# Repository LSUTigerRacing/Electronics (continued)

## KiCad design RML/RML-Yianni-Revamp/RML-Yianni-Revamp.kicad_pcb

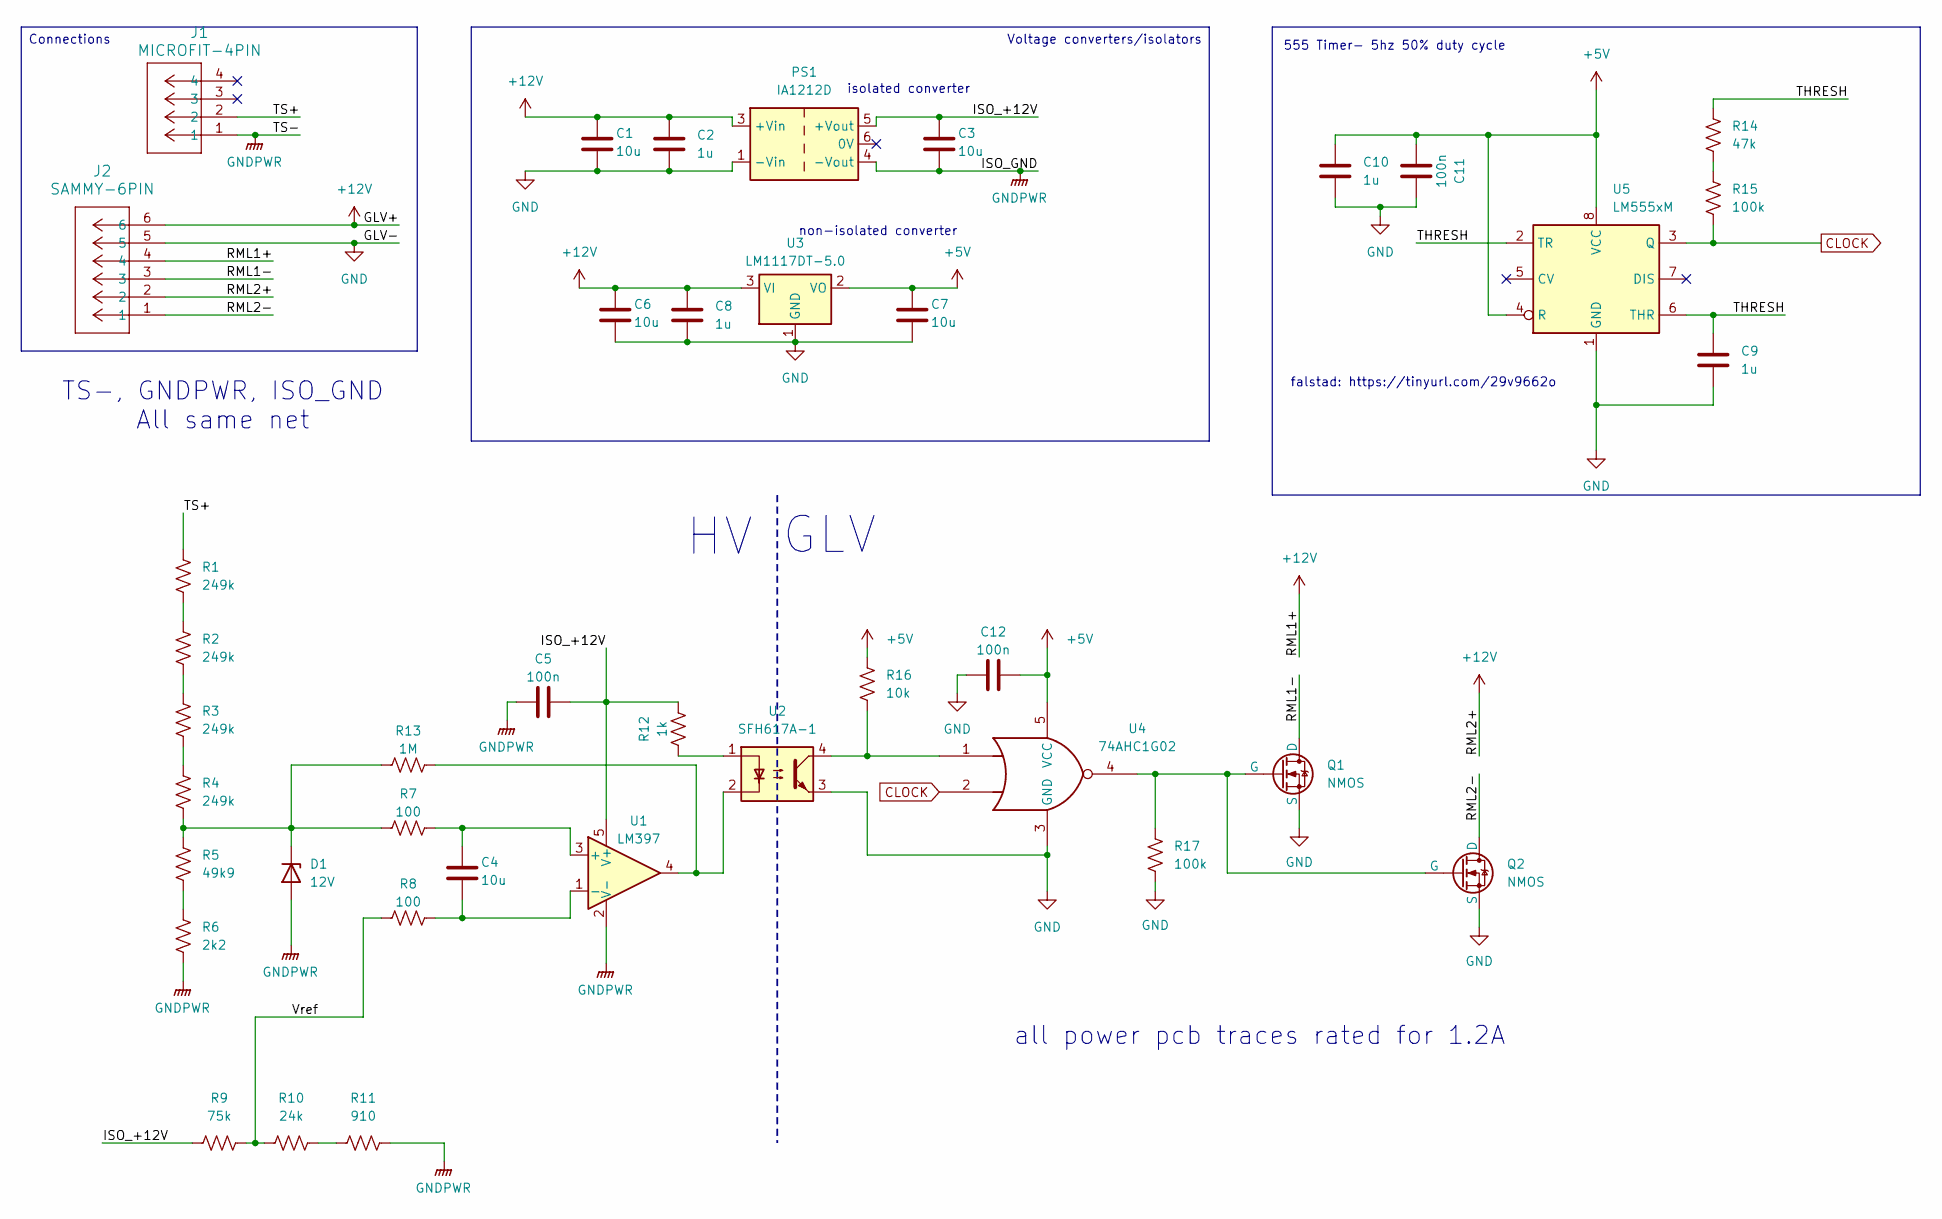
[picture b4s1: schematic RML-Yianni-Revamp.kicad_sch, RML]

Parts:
C1, C3, C4, C6, C7: 10u; C_0603_1608Metric; JLC# C70225
C2, C8, C9, C10: 1u; C_0603_1608Metric; JLC# C1592
C5, C11, C12: 100n; C_0603_1608Metric; JLC# C1590
D1: 12V; D_SOD-123; JLC# C43491
J1: MICROFIT-4PIN
J2: SAMMY-6PIN
PS1: IA1212D; Converter_DCDC_XP_POWER-IAxxxxD_THT
Q1, Q2: NMOS; SOT-23; JLC# C2590
R1, R2, R3, R4: 249k; R_1206_3216Metric; JLC C34578
R5: 49k9; R_1206_3216Metric; JLC# C18017
R6: 2k2; R_1206_3216Metric; JLC# C17948
R7, R8: 100; R_1206_3216Metric; JLC# C17901
R9: 75k; R_1206_3216Metric; JLC# C17986
R10: 24k; R_1206_3216Metric; JLC# C17960
R11: 910; R_1206_3216Metric; JLC# C137224
R12: 1k; R_1206_3216Metric; JLC# C1469
R13: 1M; R_1206_3216Metric; JLC# C17927
R14: 47k; R_1206_3216Metric; JLC# C25664
R15, R17: 100k; R_1206_3216Metric; JLC# C17900
R16: 10k; R_1206_3216Metric; JLC# C1489
U1: LM397; SOT-23-5; JLC# C132076
U2: SFH617A-1; DIP-4_W7.62mm; MOUSER SFH617A-1
U3: LM1117DT-5.0; TO-252-3_TabPin2; JLC# C354068
U4: 74AHC1G02; SOT-23-5; JLC# C7463
U5: LM555xM; SOIC-8_3.9x4.9mm_P1.27mm; JLC# C90760

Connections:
+5V: C7.1, C10.1, C11.1, C12.2, R16.1, U3.2 (VO), U4.5 (VCC), U5.4 (R), U5.8 (VCC)
+12V: C1.1, C2.1, C6.1, C8.1, J2.2, J2.4, J2.6, PS1.3 (+Vin), U3.3 (VI)
/ISO_+12V: C3.1, C5.2, PS1.5 (+Vout), R9.1, R12.2, U1.5 (V+)
/RML1-: J2.3, Q1.1 (D)
/RML2-: J2.1, Q2.1 (D)
/THRESH: C9.1, R14.1, U5.2 (TR), U5.6 (THR)
/TS+: J1.2, R1.1
/Vref: R8.1, R9.2, R10.1
CLOCK: R15.2, U4.2, U5.3 (Q)
GND: C1.2, C2.2, C6.2, C7.2, C8.2, C9.2, C10.2, C11.2, C12.1, J2.5, PS1.1 (-Vin), Q1.3 (S), Q2.3 (S), R17.1, U2.3, U3.1 (GND), U4.3 (GND), U5.1 (GND)
GNDPWR: C3.2, C5.1, D1.2 (A), J1.1, PS1.4 (-Vout), R6.2, R11.2, U1.2 (V-)
unnamed: D1.1 (K), R4.2, R5.1, R7.1, R13.1
unnamed: Q1.2 (G), Q2.2 (G), R17.2, U4.4
unnamed: R1.2, R2.1
unnamed: R2.2, R3.1
unnamed: R3.2, R4.1
unnamed: R5.2, R6.1
unnamed: R10.2, R11.1
unnamed: R12.1, U2.1
unnamed: R13.2, U1.4, U2.2
unnamed: R14.2, R15.1
unnamed: R16.2, U2.4, U4.1
unnamed: C4.1, R7.2, U1.3 (+)
unnamed: C4.2, R8.2, U1.1 (-)

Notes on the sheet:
non-isolated converter
all power pcb traces rated for 1.2A
isolated converter
GLV
555 Timer- 5hz 50% duty cycle
falstad: https://tinyurl.com/29v9662o
TS-, GNDPWR, ISO_GND All same net
Voltage converters/isolators
Connections

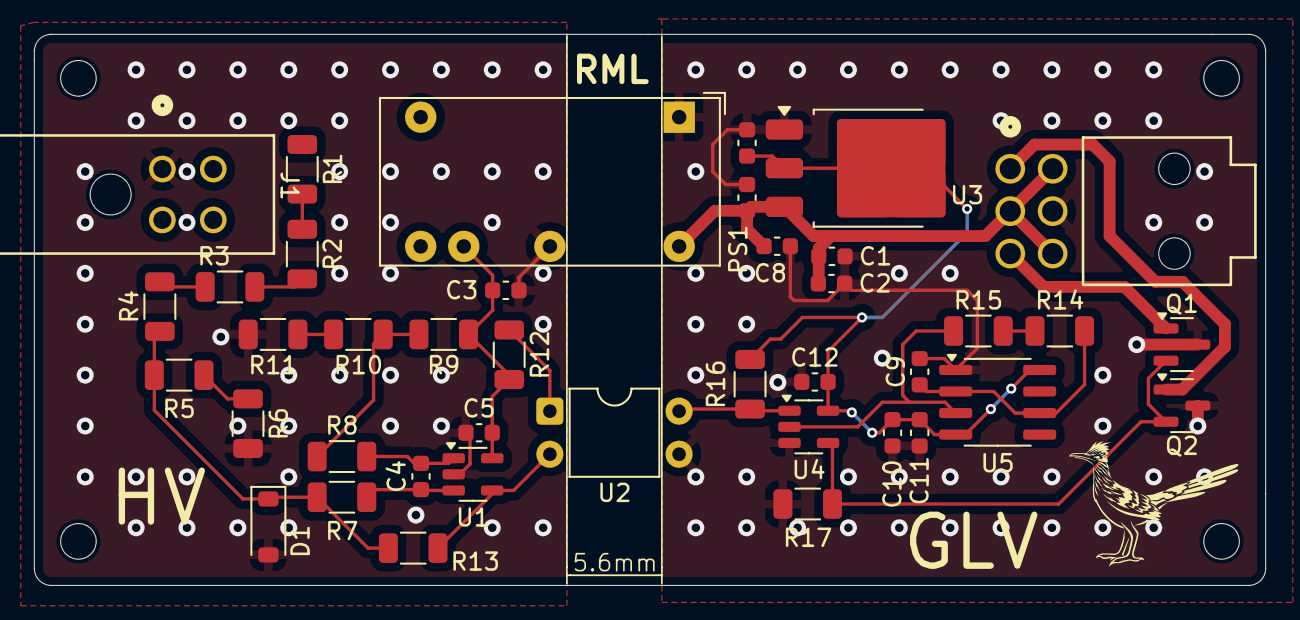
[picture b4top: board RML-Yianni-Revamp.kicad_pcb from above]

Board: 2 copper layers, 72.6 x 32.5 mm, 40 parts (0 on the bottom side), 24 nets.

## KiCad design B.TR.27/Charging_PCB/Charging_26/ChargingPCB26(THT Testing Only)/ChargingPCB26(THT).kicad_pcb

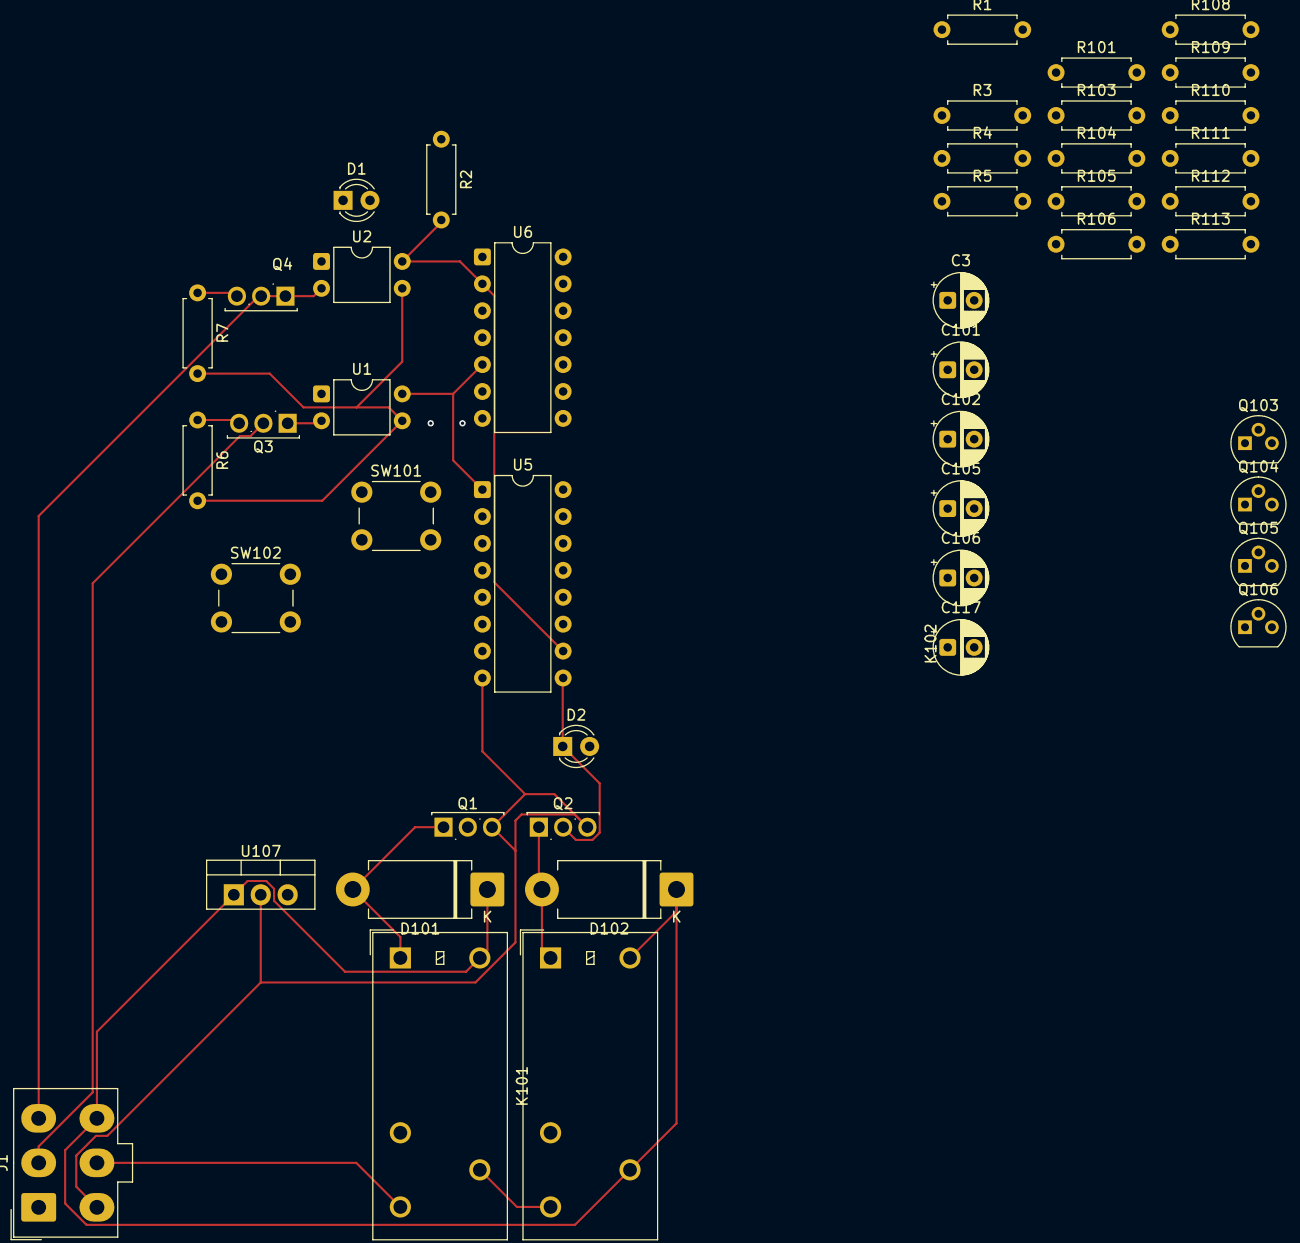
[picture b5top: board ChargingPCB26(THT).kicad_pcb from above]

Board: 2 copper layers, 46 parts (0 on the bottom side), 31 nets.

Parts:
C3, C117: 100n; CP_Radial_D5.0mm_P2.50mm
C101, C102, C106: 0.01u; CP_Radial_D5.0mm_P2.50mm
C105: 0.33u; CP_Radial_D5.0mm_P2.50mm
D1, D2: LED; LED_D3.0mm
D101, D102: D_Schottky; D_DO-201AD_P12.70mm_Horizontal
J1: Molex6pin; Molex_Mini-Fit_Jr_5566-06A_2x03_P4.20mm_Vertical
K101, K102: Relay_SPDT_Omron_G2RL-1
Q1, Q2, Q3, Q4: NMOS; TO-251-3_Vertical
Q103, Q104, Q105, Q106: Q_NPN_BEC; TO-92
R1, R2, R105, R106: 10k; R_Axial_DIN0207_L6.3mm_D2.5mm_P7.62mm_Horizontal
R3, R4: 270; R_Axial_DIN0207_L6.3mm_D2.5mm_P7.62mm_Horizontal
R5, R101: 2.2k; R_Axial_DIN0207_L6.3mm_D2.5mm_P7.62mm_Horizontal
R6, R7, R108, R109, R111, R113: 1k; R_Axial_DIN0207_L6.3mm_D2.5mm_P7.62mm_Horizontal
R103, R104, R110, R112: 100k; R_Axial_DIN0207_L6.3mm_D2.5mm_P7.62mm_Horizontal
SW101, SW102: SW_Omron_B3FS; SW_PUSH_6mm_H4.3mm
U1, U2: SFH617A-1; DIP-4_W7.62mm
U5: 74LS279; DIP-16_W7.62mm
U6: 74HC00; DIP-14_W7.62mm
U107: LM7805_TO220; TO-220-3_Vertical

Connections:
+5V: C3.1, C106.1, C117.1, R1.1, R2.1, R3.1, R4.1, R108.1, R109.1, R110.1, R111.1, R112.1, R113.1, SW101.2, SW102.2, U5.16 (VCC), U6.14 (VCC), U107.3 (VO)
+12V: C105.1, D101.1 (K), D102.1 (K), J1.6, K101.A2, K102.11, K102.A2, R101.1, U1.1, U2.1, U107.1 (VI)
/+12_Relay: J1.5, K101.14
/BMS_CSO: J1.2, Q3.2 (G), R101.2
/BMS_LV: R1.2, U1.4, U5.1 (~R), U6.5
/BMS_RESET: Q104.3 (C), R111.2, U6.4
/IMD_Error: J1.3, Q4.2 (G), R5.1
/IMD_LV: R2.2, U2.4, U5.10 (~R), U6.2
/IMD_RESET: Q106.3 (C), R113.2, U6.1
GND: C3.2, C105.2, C106.2, C117.2, J1.4, Q1.3 (S), Q2.3 (S), Q103.2 (E), Q104.2 (E), Q105.2 (E), Q106.2 (E), R5.2, R6.2, R7.2, R103.2, R104.2, U1.3, U2.3, U5.8 (GND), U6.7 (GND), U107.2 (GND)
unnamed: D1.2 (A), R3.2
unnamed: D1.1 (K), Q1.2 (G), U5.4 (Q)
unnamed: D2.2 (A), R4.2
unnamed: D2.1 (K), Q2.2 (G), U5.9 (Q)
unnamed: D101.2 (A), K101.A1, Q1.1 (D)
unnamed: D102.2 (A), K102.A1, Q2.1 (D)
unnamed: K101.11, K102.14
unnamed: Q3.1 (D), U1.2
unnamed: Q3.3 (S), R6.1
unnamed: Q4.1 (D), U2.2
unnamed: Q4.3 (S), R7.1
unnamed: Q103.1 (B), R105.1
unnamed: C101.1, Q103.3 (C), R108.2
unnamed: C101.2, Q104.1 (B), R110.2
unnamed: Q105.1 (B), R106.1
unnamed: C102.1, Q105.3 (C), R109.2
unnamed: C102.2, Q106.1 (B), R112.2
unnamed: R103.1, R105.2, SW101.1
unnamed: R104.1, R106.2, SW102.1
unnamed: U5.2 (~S), U5.3 (~S), U6.6
unnamed: U5.11 (~S), U5.12 (~S), U6.3

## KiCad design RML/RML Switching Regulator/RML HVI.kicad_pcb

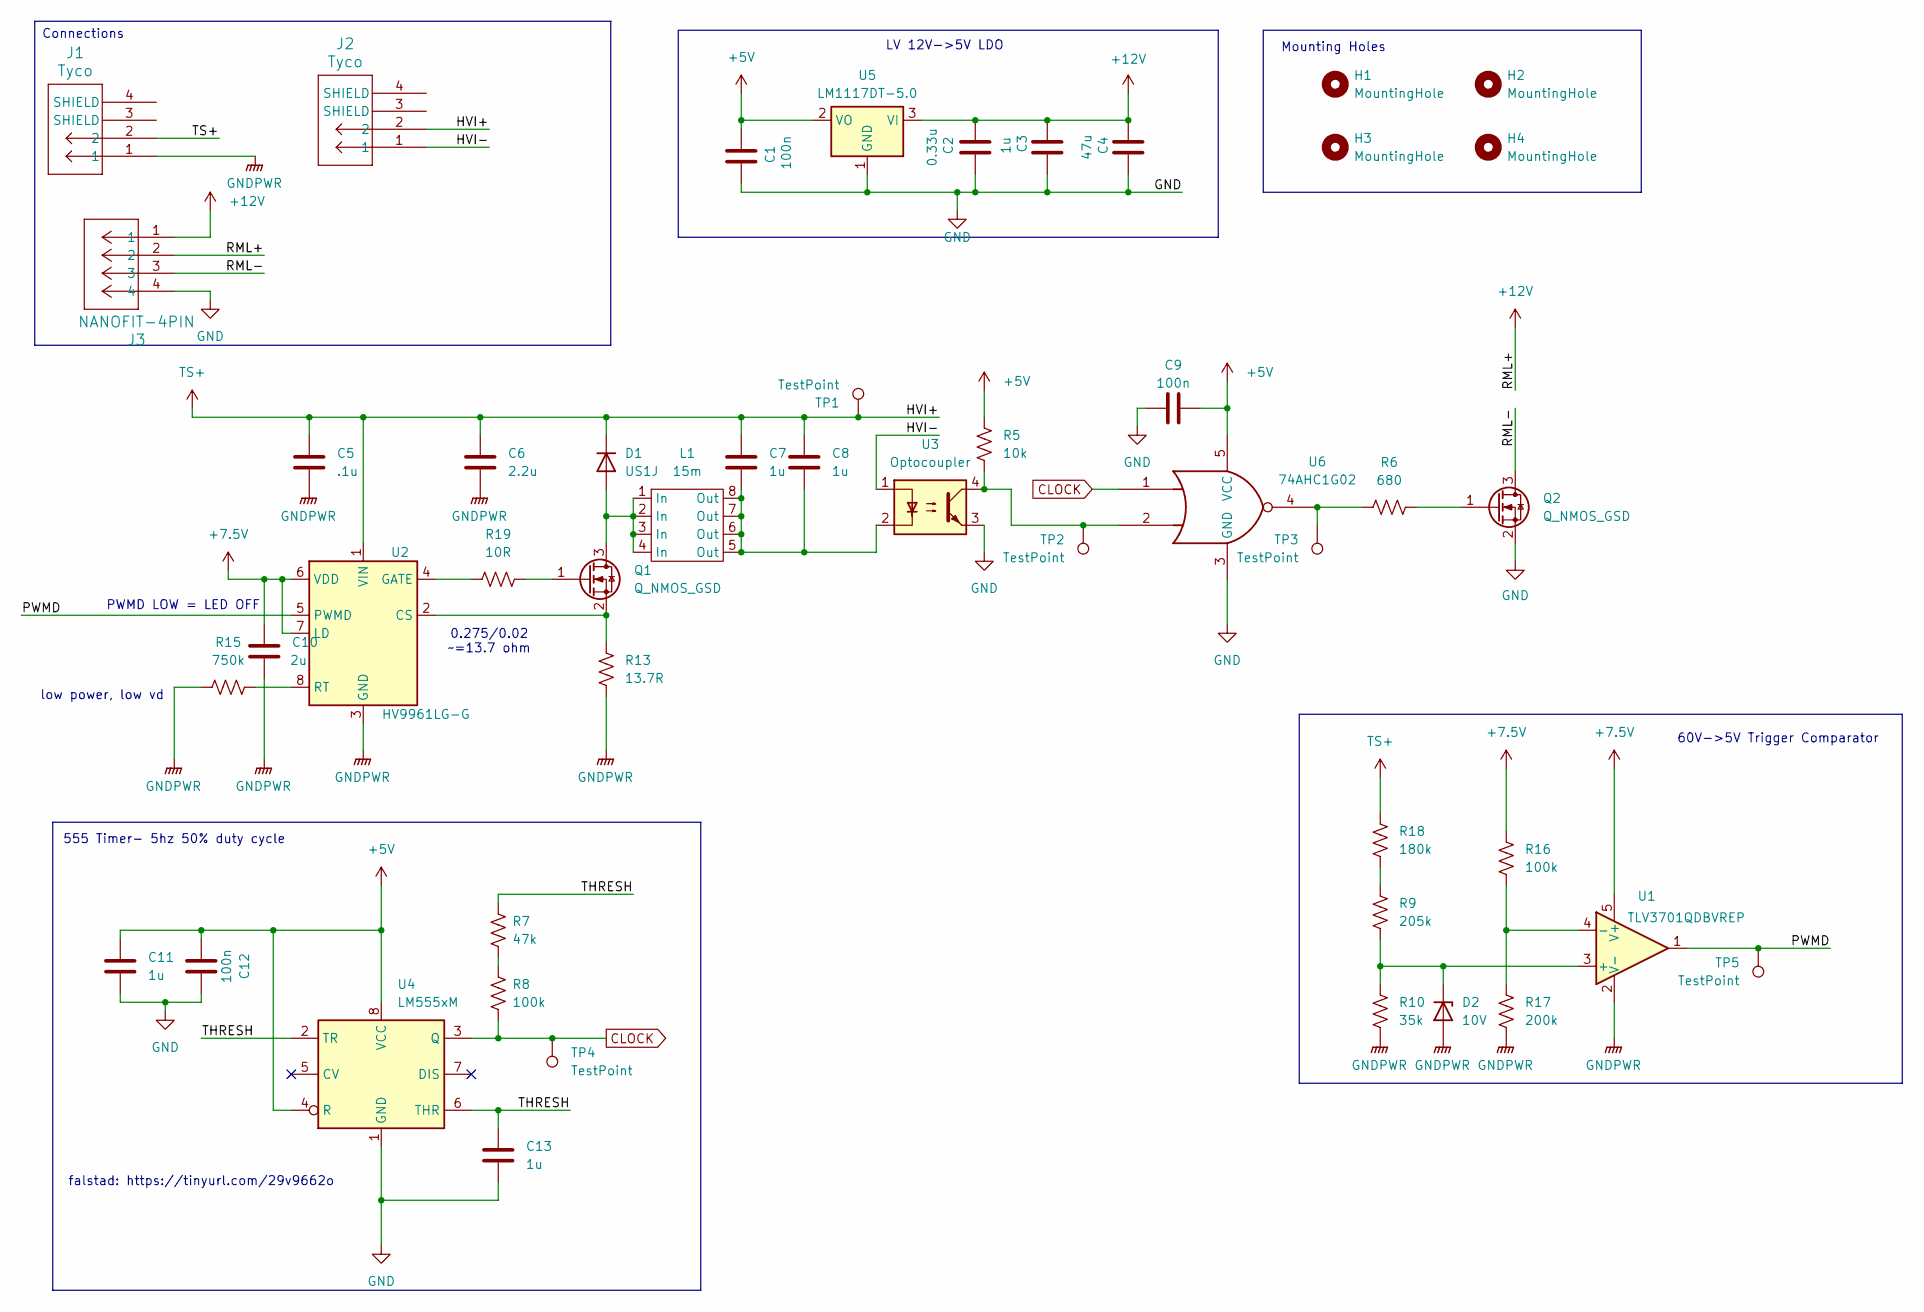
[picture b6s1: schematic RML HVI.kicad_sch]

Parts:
C1: 100n; C_0603_1608Metric_Pad1.08x0.95mm_HandSolder; JLC# C1591
C2: 0.33u; C_0603_1608Metric_Pad1.08x0.95mm_HandSolder; JLC# C282682
C3: 1u; C_0805_2012Metric_Pad1.18x1.45mm_HandSolder; JLC# C91186
C4: 47u; CP_Elec_6.3x5.4; JLC# C2836440
C5: .1u; C_1210_3225Metric; Manufacture# C1210X104JCRAC3316; Mouser# 80-C1210X104JCR3316
C6: 2.2u; CAPC6050X550N; Manufacture# CKG57NX7T2W225M500JH; Mouser# 810-CKG57NX7T2W225M
C7, C8: 1u; C_1210_3225Metric; Manufacture# KAF32GR71H105KU; Mouser# 581-KAF32GR71H105KU
C9, C12: 100n; C_0603_1608Metric; JLC# C1590
C10: 2u; C_0805_2012Metric; Manufacture# GXT21BR71C225KE01L; Mouser# 81-GXT21BR71C225KE1L
C11, C13: 1u; C_0603_1608Metric; JLC# C1592
D1: US1J; D_SMA; Mouser 637-US1J
D2: 10V; Nexperia_CFP3_SOD-123W; Manufacture# MMSZ5240C-HE3_A-08; Mouser# 78-MMSZ5240CHE3_A-08
H1, H2, H3, H4: MountingHole; MountingHole_3.2mm_M3_DIN965_Pad_TopOnly
J1, J2: Tyco; tyco
J3: NANOFIT-4PIN; Molex_Nano-Fit_105313-xx04_1x04_P2.50mm_Horizontal
L1: 15m; IND_BOURNS_SRR0908; Manufacture# SRR0908-153YL; Mouser# 652-SRR0908-153YL
Q1: Q_NMOS_GSD; TO-252-3_TabPin2; Manufacture# IPD70R1K4P7SAUMA1; Mouser# 726-IPD70R1K4P7AUMA1
Q2: Q_NMOS_GSD; SOT-23; JLC# C2590
R5: 10k; R_0805_2012Metric
R6: 680; R_0805_2012Metric; MFR# CR0805-JW-681ELF
R7: 47k; R_1206_3216Metric; JLC# C25664
R8: 100k; R_1206_3216Metric; JLC# C17900
R9: 205k; R_1210_3225Metric; Manufacture# AC1210FR-07205KL; Mouser# 603-AC1210FR-07205KL
R10: 35k; R_0402_1005Metric; Manufacture# RC0402FR-0735KL; Mouser# 603-RC0402FR-0735KL
R13: 13.7R; R_0805_2012Metric; Manufacture# RC0805FR-0713R7L; Mouser# 603-RC0805FR-0713R7L
R15: 750k; R_0805_2012Metric
R16: 100k; R_0805_2012Metric; Manufacture# RE0805FRE1010KL; Mouser# 603-RE0805FRE1010KL
R17: 200k; R_0805_2012Metric; Manufacture# AC0805FR-0720KL; Mouser# 603-AC0805FR-0720KL
R18: 180k; R_1210_3225Metric; Manufacture# RC1210FR-07180KL; Mouser# 603-RC1210FR-07180KL
R19: 10R; R_0201_0603Metric; Manufacture# 0603WAF100JT1E; Mouser# 303-0603WAF100JT1E
TP1, TP2, TP3, TP4, TP5: TestPoint; TestPoint_Pad_1.0x1.0mm
U1: TLV3701QDBVREP; SOT-23-5; Manufacture# TLV3701QDBVREP; Mouser# 595-TLV3701QDBVREP
U2: HV9961LG-G; SOIC-8_3.9x4.9mm_P1.27mm
U3: Optocoupler; Q_Wurth_WL-OCPT_LSOP4-STANDARD; Manufacture# VOLA617A-3X001T; Mouser# 78-VOLA617A-3X001T
U4: LM555xM; SOIC-8_3.9x4.9mm_P1.27mm; JLC# C90760
U5: LM1117DT-5.0; TO-252-3_TabPin2; JLC# C354068
U6: 74AHC1G02; SOT-23-5; Mouser 595-SN74AHC1G02DBE4

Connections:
+5V: C1.2, C9.2, C11.1, C12.1, R5.1, U4.4 (R), U4.8 (VCC), U5.2 (VO), U6.5 (VCC)
+7.5V: C10.1, R16.1, U1.5 (V+), U2.6 (VDD), U2.7 (LD)
+12V: C2.1, C3.1, C4.1, J3.1, J3.2, U5.3 (VI)
/HVI-: J2.1, U3.1
/PWMD: TP5.1, U1.1, U2.5 (PWMD)
/RML-: J3.3, Q2.3 (D)
/THRESH: C13.1, R7.1, U4.2 (TR), U4.6 (THR)
CLOCK: R8.2, TP4.1, U4.3 (Q), U6.1
GND: C1.1, C2.2, C3.2, C4.2, C9.1, C11.2, C12.2, C13.2, J3.4, Q2.2 (S), U3.3, U4.1 (GND), U5.1 (GND), U6.3 (GND)
GNDPWR: C5.2, C6.2, C10.2, D2.2 (A), J1.1, R10.2, R13.2, R15.1, R17.2, U1.2 (V-), U2.3 (GND)
unnamed: C7.2, C8.2, L1.5 (Out), L1.6 (Out), L1.7 (Out), L1.8 (Out), U3.2
unnamed: D1.2 (A), L1.1 (In), L1.2 (In), L1.3 (In), L1.4 (In), Q1.3 (D)
unnamed: D2.1 (K), R9.2, R10.1, U1.3 (+)
unnamed: Q1.1 (G), R19.2
unnamed: Q1.2 (S), R13.1, U2.2 (CS)
unnamed: Q2.1 (G), R6.2
unnamed: R5.2, TP2.1, U3.4, U6.2
unnamed: R6.1, TP3.1, U6.4
unnamed: R7.2, R8.1
unnamed: R9.1, R18.2
unnamed: R16.2, R17.1, U1.4 (-)
unnamed: R19.1, U2.4 (GATE)
unnamed: R15.2, U2.8 (RT)
TS+: C5.1, C6.1, C7.1, C8.1, D1.1 (K), J1.2, J2.2, R18.1, TP1.1, U2.1 (VIN)

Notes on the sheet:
555 Timer- 5hz 50% duty cycle
Mounting Holes
0.275/0.02 ~=13.7 ohm
PWMD LOW = LED OFF
60V->5V Trigger Comparator
falstad: https://tinyurl.com/29v9662o
low power, low vd
LV 12V->5V LDO
Connections

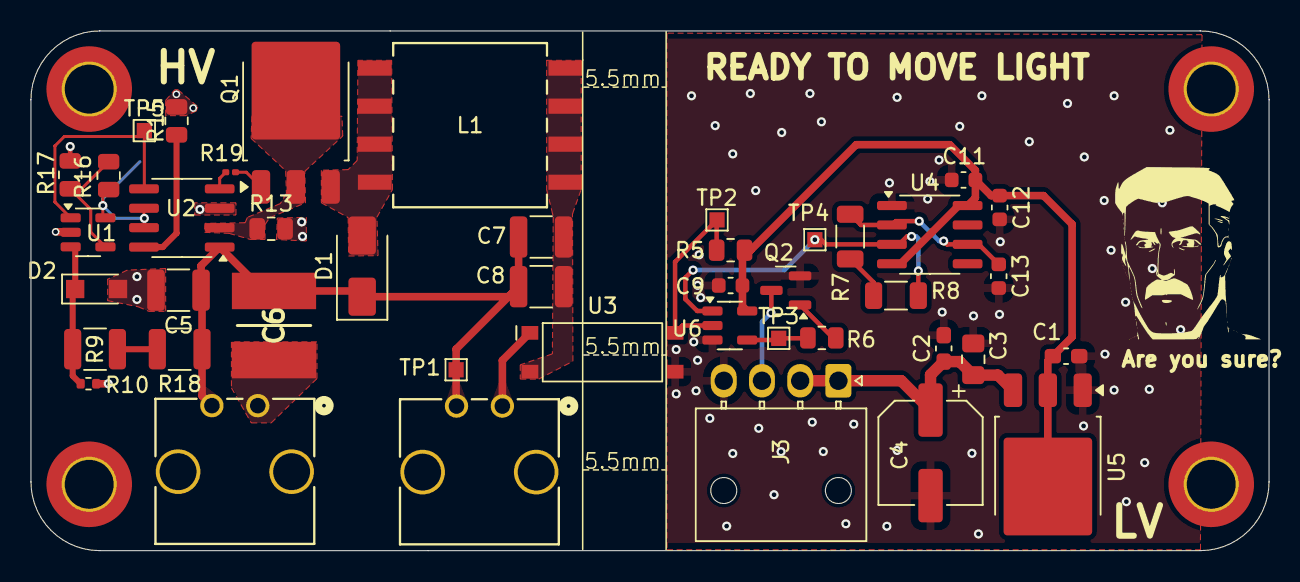
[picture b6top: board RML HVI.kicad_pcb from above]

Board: 2 copper layers, 81.0 x 34.0 mm, 48 parts (1 on the bottom side), 24 nets.
